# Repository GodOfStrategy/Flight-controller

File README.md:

# Flight-controller
A custom Flight controller to control a rocket with TVC! It uses a STM32 and other peripherals like power management, battery charging etc. to make it a fully functional controller, with LiPo support. I decided to make this because our school has "Aerobay" lab, which has these foam cutout diy airplanes from rudderraider.com or something like that, but It has no flight computer, it only has basic controls, and no way to measure flight data.
This is my schematic
This is how my PCB looks:
This how my Assembled PCB is supposed to look like:

This is my BoM (also in a .csv file in the repo): 
| Designator | Footprint | Value | LCSC Part # | Generic Name | Qty | Source | Unit Price ($) | Product Link | Total ($) |
|------------|-----------|-------|-------------|--------------|-----|--------|----------------|--------------|-----------|
| C1 | 0402 | 47 nF | C82219 | Capacitors | 20 | JLCPCB | 0.068 | https://jlcpcb.com/partdetail/83376-0402B473K500NT/C82219 | 1.36 |
| C2, C3 | 0402 | 22 uF | C15525 | Capacitors | 20 | JLCPCB | 0.394 | https://jlcpcb.com/partdetail/16204-CL05A106MQ5NUNC/C15525 | 7.88 |
| C4 | 0805 | 10 uF | C124129 | Capacitors | 5 | JLCPCB | 1.0915 | https://jlcpcb.com/partdetail/125403-GRM21BR61A476ME15L/C124129 | 5.46 |
| C10, C11, C16, C17, C9 | 0805 | 10 uF | C45783 | Capacitors | 18 | JLCPCB | 2.1114 | https://jlcpcb.com/partdetail/46786-CL21A226MAQNNNE/C45783 | 38.00 |
| C12, C13, C14, C5, C8 | 0805 | 10 uF | C440198 | Capacitors | 10 | JLCPCB | 0.912 | https://jlcpcb.com/partdetail/439567-GRM21BR61H106KE43L/C440198 | 9.12 |
| C15, C18–C21, C26, C28–C32, C7 | 0402 | 100 nF | C1525 | Capacitors | 34 | JLCPCB | 0.204 | https://jlcpcb.com/partdetail/1877-CL05B104KO5NNNC/C1525 | 6.94 |
| C22, C23 | 0402 | 20 pF | C1554 | Capacitors | 20 | JLCPCB | 0.066 | https://jlcpcb.com/partdetail/1906-0402CG200J500NT/C1554 | 1.32 |
| C24, C25 | 0402 | 6.8 PF | C1576 | Capacitors | 20 | JLCPCB | 0.048 | https://jlcpcb.com/partdetail/1928-0402CG6R8C500NT/C1576 | 0.96 |
| C27 | 0402 | 2.2 uF | C12530 | Capacitors | 20 | JLCPCB | 0.154 | https://jlcpcb.com/partdetail/13164-CL05A225MQ5NSNC/C12530 | 3.08 |
| C33–C36, C6 | 0402 | 1 uF | C52923 | Capacitors | 20 | JLCPCB | 0.282 | https://jlcpcb.com/partdetail/53938-CL05A105KA5NQNC/C52923 | 5.64 |
| CARD1 | SMD | TF‑01A | C91145 | SD Card Slot | 2 | JLCPCB | 0.3802 | https://jlcpcb.com/partdetail/Korean_HropartsElec-TF01A/C91145 | 0.76 |
| D1 | 0805 | LED | C2293 | LED | 20 | JLCPCB | 0.244 | https://jlcpcb.com/partdetail/Hubei_KENTOElec-KT0805B/C2293 | 4.88 |
| J1 | 插件,P=2.54mm | Screw_Terminal_01x02 | C557685 | Screw Terminal | 2 | JLCPCB | 0.48 | https://jlcpcb.com/partdetail/Ningbo_Xinlaiya_Elec-XY308_2_542P/C557685 | 0.96 |
| L1 | 1210 | 1 uH | C99412 | Inductor | 6 | JLCPCB | 0.696 | https://jlcpcb.com/partdetail/100626-CMI322513U1R0KT/C99412 | 4.18 |
| L2 | 1008 | 1.5 uH | C5289259 | Inductor | 6 | JLCPCB | 0.2256 | https://jlcpcb.com/partdetail/XR-XRNR252010_1_5uHN/C5289259 | 1.35 |
| L3 | 1210 | 5.6 uH | C87563 | Inductor | 6 | JLCPCB | 0.2748 | https://jlcpcb.com/partdetail/TDK-NLV32T_5R6JPF/C87563 | 1.65 |
| L4 | 0603 | FCM1608KF‑601T03 | C141723 | Ferrite Bead | 20 | JLCPCB | 0.202 | https://jlcpcb.com/partdetail/TAITECH-FCM1608KF601T03/C141723 | 4.04 |
| R1, R2 | 0402 | 5.1K | C25905 | Resistors | 20 | JLCPCB | 0.018 | https://jlcpcb.com/partdetail/26648-0402WGF5101TCE/C25905 | 0.36 |
| R9 | 0201 | 30.1K | C320818 | Resistors | 20 | JLCPCB | 0.012 | https://jlcpcb.com/partdetail/301723-RC01W3012FT/C320818 | 0.24 |
| R10 | 0201 | 383 | C423551 | Resistors | 20 | JLCPCB | 0.012 | https://jlcpcb.com/partdetail/416501-0201WMF3830TEE/C423551 | 0.24 |
| R11 | 0201 | 5.23K | C332546 | Resistors | 20 | JLCPCB | 0.022 | https://jlcpcb.com/partdetail/RALEC-RTT015231FTH/C332546 | 0.44 |
| R12–R22 | 0201 | 10K | C7467266 | Resistors | 40 | JLCPCB | 0.032 | https://jlcpcb.com/partdetail/FOJAN-FRC0201J103TS/C7467266 | 1.28 |
| R14 | 0805 | 100K | C149504 | Resistors | 20 | JLCPCB | 0.064 | https://jlcpcb.com/partdetail/160838-0805W8F1003T5E/C149504 | 1.28 |
| R15 | 0201 | 22.1K | C384418 | Resistors | 20 | JLCPCB | 0.02 | https://jlcpcb.com/partdetail/Walsin_TechCorp-WR02X2212FAL/C384418 | 0.40 |
| SW1, SW2 | SMD, 4x3mm | TS‑1088‑AR02016 | C720477 | Switches | 8 | JLCPCB | 0.4408 | https://jlcpcb.com/partdetail/XUNPU-TS_1088AR02016/C720477 | 3.53 |
| U1 | VQFN‑24‑EP(4x4) | BQ25883RGER | C544362 | Battery Management | 2 | JLCPCB | 8.189 | https://jlcpcb.com/partdetail/TexasInstruments-BQ25883RGER/C544362 | 16.38 |
| U2 | VQFN‑15‑HR(2.5x3) | TPS63070RNMR | C109322 | Buck Converter (5V) | 2 | JLCPCB | 2.6384 | https://jlcpcb.com/partdetail/TexasInstruments-TPS63070RNMR/C109322 | 5.28 |
| U3 | SOT‑23‑6‑THIN | LMR51430 | C5219261 | Buck Converter | 2 | JLCPCB | 1.73 | https://jlcpcb.com/partdetail/TexasInstruments-LMR51430YFDDCR/C5219261 | 3.46 |
| U4 | LGA‑10(2x2) | BMP580 | C22391138 | Barometer | 2 | JLCPCB | 2.6674 | https://jlcpcb.com/partdetail/BoschSensortec-BMP580/C22391138 | 5.33 |
| U5 | LGA‑14(3x2.5) |ICM-45686|C22459454|IMU|2|JLCPCB|$25.8362|https://www.lcsc.com/product-detail/C22459454.html|
|U6|LQFP-64_10x10mm_P0.5mm|STM32F722RET6|C118207|MCU|2|JCLPCB|$12.5220|https://www.lcsc.com/product-detail/C118207.html|
| USB1 | USB-C-SMD_TYPE-C-16PIN-2MD-073 | TYPE-C 16PIN 2MD | C2765186 | USB Type-C Receptacle | 2 | JLCPCB | $0.2205 | https://www.lcsc.com/product-detail/C2765186.html | 
| X1 | CRYSTAL-SMD_4P-L3.2-W2.5-BL | X322525MOB4SI | C9006 | Crystal Oscillator | 2 | JLCPCB | $0.6180| https://www.lcsc.com/product-detail/C9006.html| 
| X2 | FC-135R_L3.2-W1.5 | Q13FC1350000400 | C32346 | Tuning Fork Crystal | 2 | JLCPCB | $0.8635 | https://www.lcsc.com/product-detail/C32346.html | 
| **Grand Total** |  |  |  |  |  |  |  |  | **206.47** |

[bom.csv](https://github.com/user-attachments/files/29258043/bom.csv)

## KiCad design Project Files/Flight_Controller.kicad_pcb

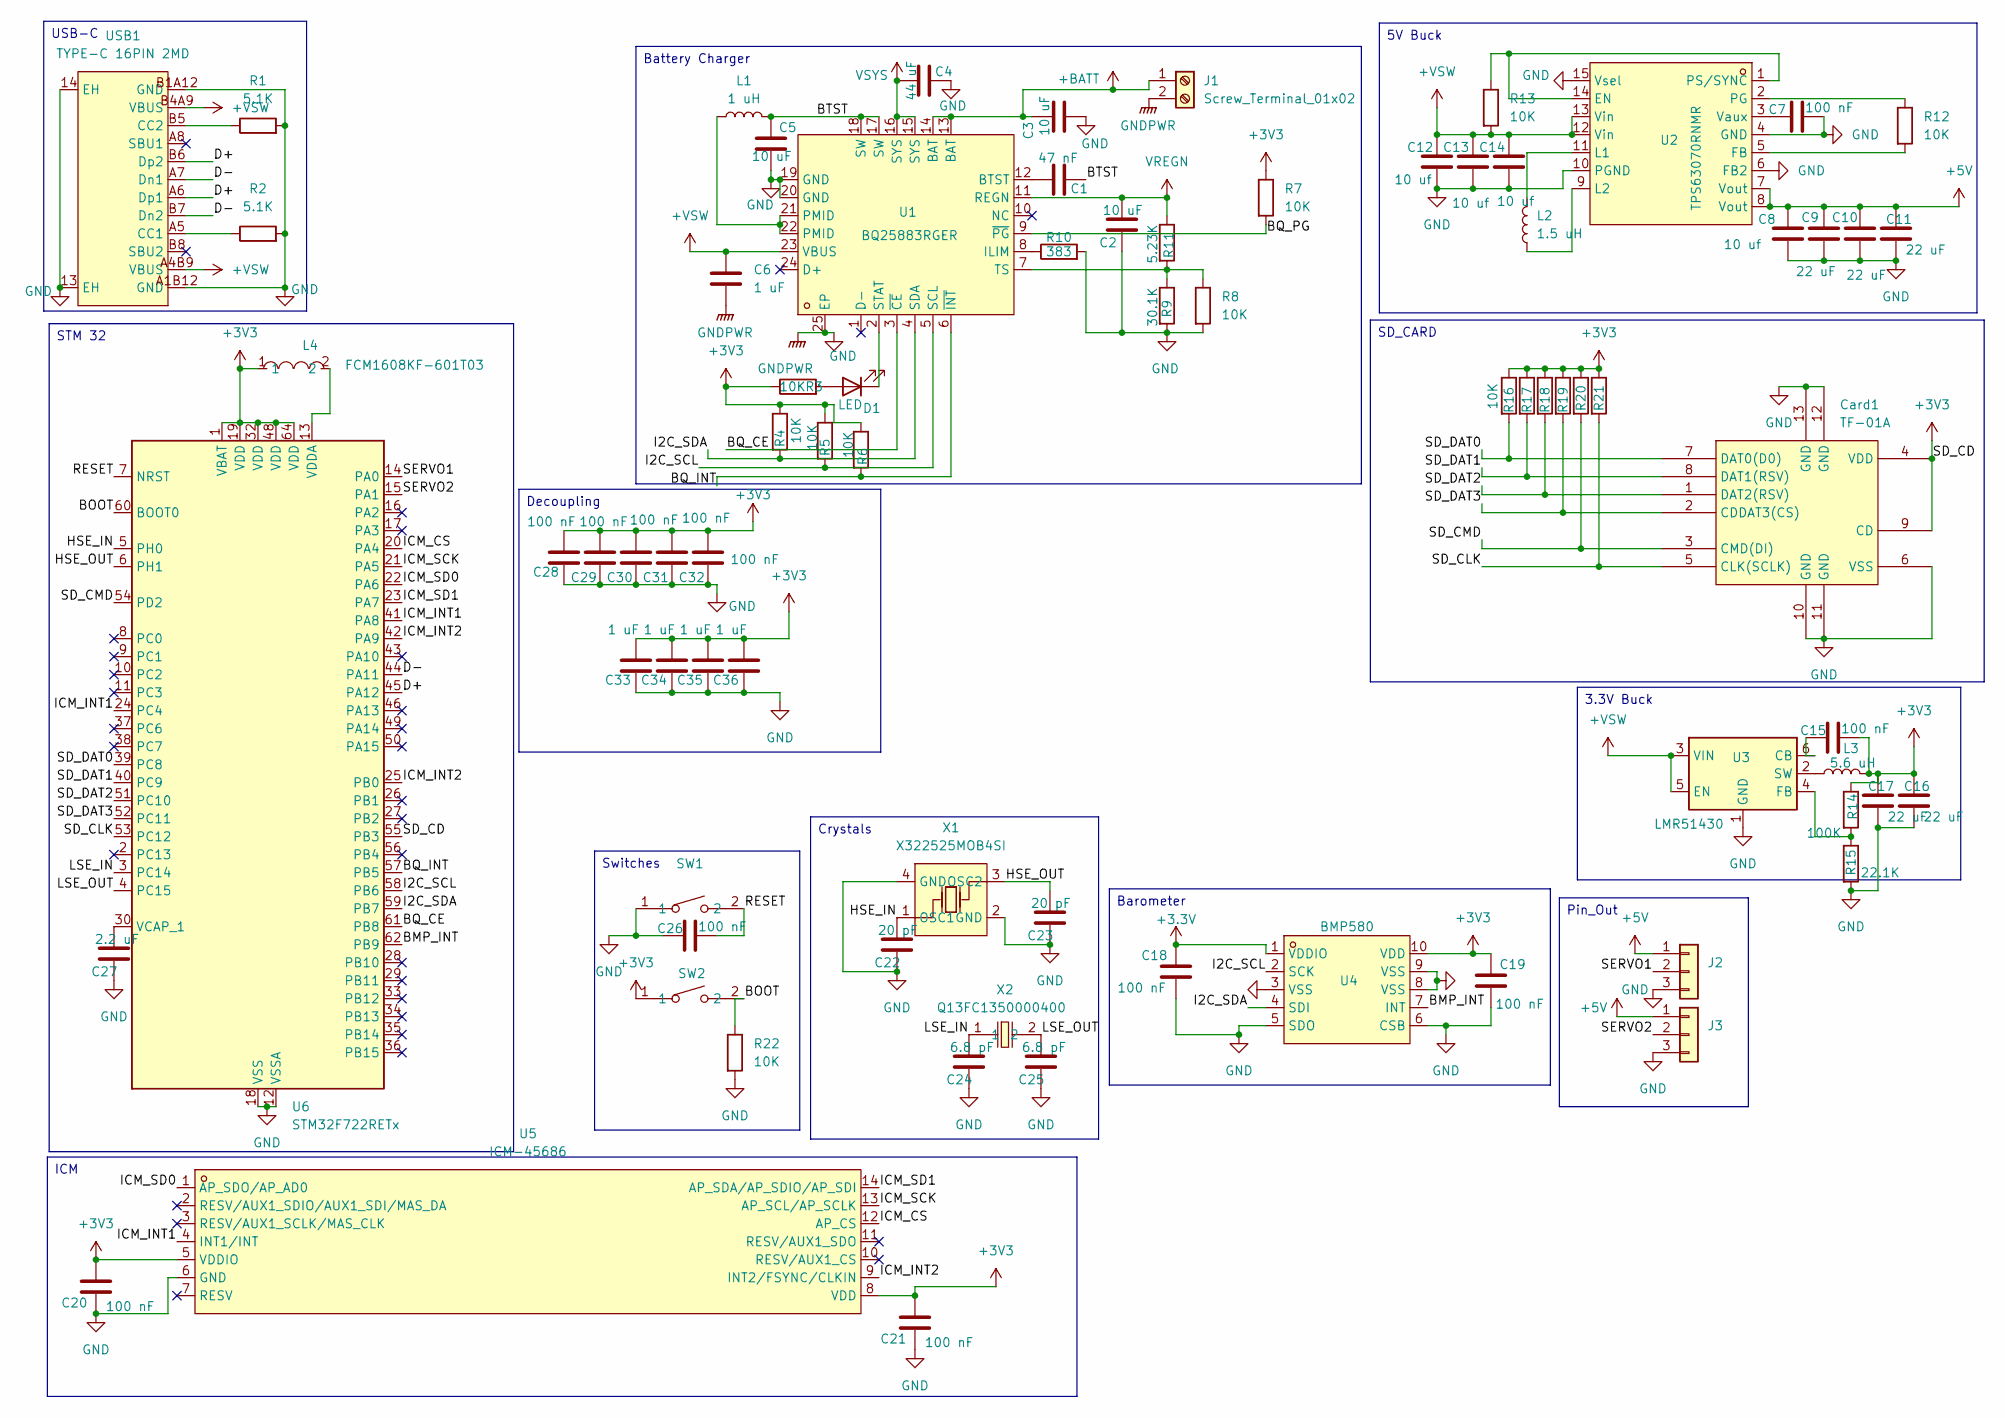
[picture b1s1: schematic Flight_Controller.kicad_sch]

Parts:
C1: 47 nF; C_0402_1005Metric
C2, C3: 10 uF; C_0402_1005Metric
C4: 44 uF; C_0805_2012Metric
C5: 10 uF; C_0805_2012Metric
C6, C33, C34, C35, C36: 1 uF; C_0402_1005Metric
C7, C15, C18, C19, C20, C21, C26, C28, C29, C30, C31, C32: 100 nF; C_0402_1005Metric
C8, C12, C13, C14: 10 uf; C_0805_2012Metric
C9, C10, C11, C16, C17: 22 uF; C_0805_2012Metric
C22, C23: 20 pF; C_0402_1005Metric
C24, C25: 6.8 pF; C_0402_1005Metric
C27: 2.2 uF; C_0402_1005Metric
Card1: TF-01A; TF-SMD_TF-01A; MPN TF-01A; LCSC Part C91145
D1: LED; LED_0805_2012Metric
J1: Screw_Terminal_01x02; TerminalBlock_Xinya_XY308-2.54-2P_1x02_P2.54mm_Horizontal
J2, J3: Conn_01x03; PinHeader_1x03_P2.54mm_Vertical
L1: 1 uH; L_1210_3225Metric
L2: 1.5 uH; L_1210_3225Metric
L3: 5.6 uH; L_1210_3225Metric
L4: FCM1608KF-601T03; L0603; MPN FCM1608KF-601T03; LCSC Part C141723
R1, R2: 5.1K; R_0402_1005Metric
R3, R4, R5, R6, R7, R8, R12, R13, R16, R17, R18, R19, R20, R21, R22: 10K; R_0201_0603Metric
R9: 30.1K; R_0201_0603Metric
R10: 383; R_0201_0603Metric
R11: 5.23K; R_0201_0603Metric
R14: 100K; R_0805_2012Metric
R15: 22.1K; R_0201_0603Metric
SW1, SW2: TS-1088-AR02016; SW-SMD_L3.9-W3.0-P4.45; MPN TS-1088-AR02016; LCSC Part C720477
U1: BQ25883RGER; VFQFPN-24_L4.0-W4.0-P0.50-BL-EP2.8; MPN BQ25883RGER; LCSC Part C544362
U2: TPS63070RNMR; VQFN-15_L3.0-W2.5-P0.50-BL; MPN TPS63070RNMR; LCSC Part C109322
U3: LMR51430; SOT-23-6
U4: BMP580; LGA-10_L2.0-W2.0-P0.50-TL_BMP580; MPN BMP580; LCSC Part C22391138
U5: ICM-45686; LGA-14_L3.0-W2.5-P0.50-TL; MPN ICM-45686; LCSC Part C22459454
U6: STM32F722RETx; LQFP-64_10x10mm_P0.5mm
USB1: TYPE-C 16PIN 2MD; USB-C-SMD_TYPE-C-16PIN-2MD-073; MPN TYPE-C 16PIN 2MD(073); LCSC Part C2765186
X1: X322525MOB4SI; CRYSTAL-SMD_4P-L3.2-W2.5-BL; MPN X322525MOB4SI; LCSC Part C9006
X2: Q13FC1350000400; FC-135R_L3.2-W1.5; MPN Q13FC13500004; LCSC Part C32346

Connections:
+3.3V: C18.2, U4.1 (VDDIO)
+3V3: C15.1, C16.1, C17.1, C19.1, C20.1, C21.1, C28.1, C29.1, C30.1, C31.1, C32.1, C33.1, C34.1, C35.1, C36.1, Card1.4 (VDD), Card1.9 (CD), L3.2, L4.1, R3.1, R4.1, R5.1, R6.1, R7.1, R14.1, R16.1, R17.1, R18.1, R19.1, R20.1, R21.1, SW2.1, U4.10 (VDD), U5.5 (VDDIO), U5.8 (VDD), U6.1 (VBAT), U6.19 (VDD), U6.32 (VDD), U6.48 (VDD), U6.55 (PB3), U6.64 (VDD)
+5V: C8.1, C9.1, C10.1, C11.1, J2.1, J3.1, U2.7 (Vout), U2.8 (Vout)
+BATT: C3.1, J1.1, U1.13 (BAT), U1.14 (BAT)
+VSW: C6.1, C12.1, C13.1, C14.1, R13.2, U1.23 (VBUS), U2.12 (Vin), U2.13 (Vin), U3.3 (VIN), U3.5 (EN), USB1.A4B9 (VBUS), USB1.B4A9 (VBUS)
/BMP_INT: U4.7 (INT), U6.62 (PB9)
/BOOT: R22.1, SW2.2, U6.60 (BOOT0)
/BQ_CE: U1.3 (~CE), U6.61 (PB8)
/BQ_INT: R6.2, U1.6 (~INT), U6.57 (PB5)
/BQ_PG: R7.2, U1.9 (~PG)
/BTST: C1.1, C5.1, L1.2, U1.17 (SW), U1.18 (SW)
/D+: U6.45 (PA12), USB1.A6 (Dp1), USB1.B6 (Dp2)
/D-: U6.44 (PA11), USB1.A7 (Dn1), USB1.B7 (Dn2)
/HSE_IN: C22.1, U6.5 (PH0), X1.1 (OSC1)
/HSE_OUT: C23.1, U6.6 (PH1), X1.3 (OSC2)
/I2C_SCL: R5.2, U1.5 (SCL), U4.2 (SCK), U6.58 (PB6)
/I2C_SDA: R4.2, U1.4 (SDA), U4.4 (SDI), U6.59 (PB7)
/ICM_CS: U5.12 (AP_CS), U6.20 (PA4)
/ICM_INT1: U5.4 (INT1/INT), U6.24 (PC4), U6.41 (PA8)
/ICM_INT2: U5.9 (INT2/FSYNC/CLKIN), U6.25 (PB0), U6.42 (PA9)
/ICM_SCK: U5.13 (AP_SCL/AP_SCLK), U6.21 (PA5)
/ICM_SD0: U5.1 (AP_SDO/AP_AD0), U6.22 (PA6)
/ICM_SD1: U5.14 (AP_SDA/AP_SDIO/AP_SDI), U6.23 (PA7)
/LSE_IN: C24.1, U6.3 (PC14), X2.1
/LSE_OUT: C25.1, U6.4 (PC15), X2.2
/RESET: C26.1, SW1.2, U6.7 (NRST)
/SD_CLK: Card1.5 (CLK(SCLK)), R21.2, U6.53 (PC12)
/SD_CMD: Card1.3 (CMD(DI)), R20.2, U6.54 (PD2)
/SD_DAT0: Card1.7 (DAT0(D0)), R16.2, U6.39 (PC8)
/SD_DAT1: Card1.8 (DAT1(RSV)), R17.2, U6.40 (PC9)
/SD_DAT2: Card1.1 (DAT2(RSV)), R18.2, U6.51 (PC10)
/SD_DAT3: Card1.2 (CDDAT3(CS)), R19.2, U6.52 (PC11)
/SERVO1: J2.2, U6.14 (PA0)
/SERVO2: J3.2, U6.15 (PA1)
GND: C2.2, C3.2, C4.2, C5.2, C6.2, C7.1, C8.2, C9.2, C10.2, C11.2, C12.2, C13.2, C14.2, C16.2, C17.2, C18.1, C19.2, C20.2, C21.2, C22.2, C23.2, C24.2, C25.2, C26.2, C27.2, C28.2, C29.2, C30.2, C31.2, C32.2, C33.2, C34.2, C35.2, C36.2, Card1.6 (VSS), Card1.10 (GND), Card1.11 (GND), Card1.12 (GND), Card1.13 (GND), J1.2, J2.3, J3.3, R1.2, R2.2, R8.2, R9.2, R10.2, R15.2, R22.2, SW1.1, U1.19 (GND), U1.20 (GND), U1.25 (EP), U2.4 (GND), U2.6 (FB2), U2.10 (PGND), U2.15 (Vsel), U3.1 (GND), U4.3 (VSS), U4.5 (SDO), U4.6 (CSB), U4.8 (VSS), U4.9 (VSS), U5.6 (GND), U6.12 (VSSA), U6.18 (VSS), U6.31 (VSS), U6.47 (VSS), U6.63 (VSS), USB1.13 (EH), USB1.14 (EH), USB1.A1B12 (GND), USB1.B1A12 (GND), X1.2 (GND), X1.4 (GND)
unnamed: D1.2 (A), R3.2
unnamed: D1.1 (K), U1.2 (STAT)
unnamed: L1.1, U1.21 (PMID), U1.22 (PMID)
unnamed: C1.2, U1.12 (BTST)
unnamed: R10.1, U1.8 (ILIM)
unnamed: R8.1, R9.1, R11.2, U1.7 (TS)
unnamed: R13.1, U2.1 (PS/SYNC), U2.14 (EN)
unnamed: R12.2, U2.5 (FB)
unnamed: L2.2, U2.11 (L1)
unnamed: L2.1, U2.9 (L2)
unnamed: R12.1, U2.2 (PG)
unnamed: C7.2, U2.3 (Vaux)
unnamed: C15.2, U3.6 (CB)
unnamed: R14.2, R15.1, U3.4 (FB)
unnamed: L3.1, U3.2 (SW)
unnamed: C27.1, U6.30 (VCAP_1)
unnamed: L4.2, U6.13 (VDDA)
unnamed: R2.1, USB1.A5 (CC1)
unnamed: R1.1, USB1.B5 (CC2)
VREGN: C2.1, R11.1, U1.11 (REGN)
VSYS: C4.1, U1.15 (SYS), U1.16 (SYS)

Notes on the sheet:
5V Buck
Barometer
SD_CARD
3.3V Buck
ICM
Switches
STM 32
USB-C
Battery Charger
Decoupling
Crystals
Pin_Out

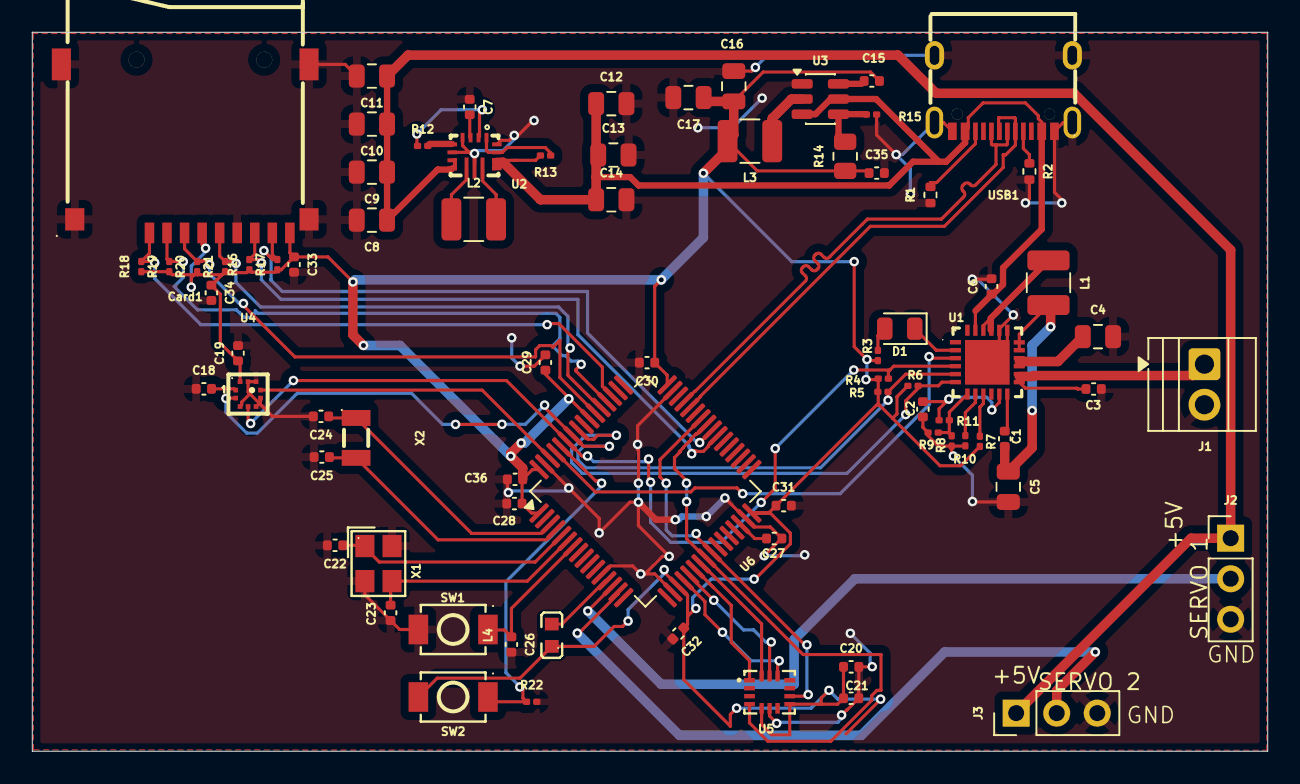
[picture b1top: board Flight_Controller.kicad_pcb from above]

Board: 2 copper layers, 77.4 x 45.1 mm, 78 parts (0 on the bottom side), 56 nets.

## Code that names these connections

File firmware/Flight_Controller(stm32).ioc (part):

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Mcu.Name=STM32F722R(C-E)Tx
Mcu.Package=LQFP64
Mcu.UserName=STM32F722RETx
PA0-WKUP.Signal=S_TIM2_CH1_ETR
PA1.Signal=S_TIM2_CH2
PA11.Mode=Host_Only
PA11.Signal=USB_OTG_FS_DM
PA12.Mode=Host_Only
PA12.Signal=USB_OTG_FS_DP
PA4.Mode=NSS_Signal_Hard_Output
PA4.Signal=SPI1_NSS
PA5.Mode=Full_Duplex_Master
PA5.Signal=SPI1_SCK
PA6.Mode=Full_Duplex_Master
PA6.Signal=SPI1_MISO
PA7.Mode=Full_Duplex_Master
PA7.Signal=SPI1_MOSI
PB0.Signal=GPXTI0
PB3.Signal=GPIO_Input
PB5.Signal=GPXTI5
PB6.Mode=I2C
PB6.Signal=I2C1_SCL
PB7.Mode=I2C
PB7.Signal=I2C1_SDA
PB8.Signal=GPIO_Output
PC10.Mode=SD_4_bits_Wide_bus
PC10.Signal=SDMMC1_D2
PC11.Mode=SD_4_bits_Wide_bus
PC11.Signal=SDMMC1_D3
PC12.Mode=SD_4_bits_Wide_bus
PC12.Signal=SDMMC1_CK
PC14-OSC32_IN.Mode=LSE-External-Oscillator
PC14-OSC32_IN.Signal=RCC_OSC32_IN
PC15-OSC32_OUT.Mode=LSE-External-Oscillator
PC15-OSC32_OUT.Signal=RCC_OSC32_OUT
PC4.Signal=GPXTI4
PC8.Mode=SD_4_bits_Wide_bus
PC8.Signal=SDMMC1_D0
PC9.Mode=SD_4_bits_Wide_bus
PC9.Signal=SDMMC1_D1
PD2.Mode=SD_4_bits_Wide_bus
PD2.Signal=SDMMC1_CMD
PH0-OSC_IN.Mode=HSE-External-Oscillator
PH0-OSC_IN.Signal=RCC_OSC_IN
PH1-OSC_OUT.Mode=HSE-External-Oscillator
PH1-OSC_OUT.Signal=RCC_OSC_OUT
RCC.HSE_VALUE=25000000
board=custom

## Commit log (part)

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2026-06-17 Create a
